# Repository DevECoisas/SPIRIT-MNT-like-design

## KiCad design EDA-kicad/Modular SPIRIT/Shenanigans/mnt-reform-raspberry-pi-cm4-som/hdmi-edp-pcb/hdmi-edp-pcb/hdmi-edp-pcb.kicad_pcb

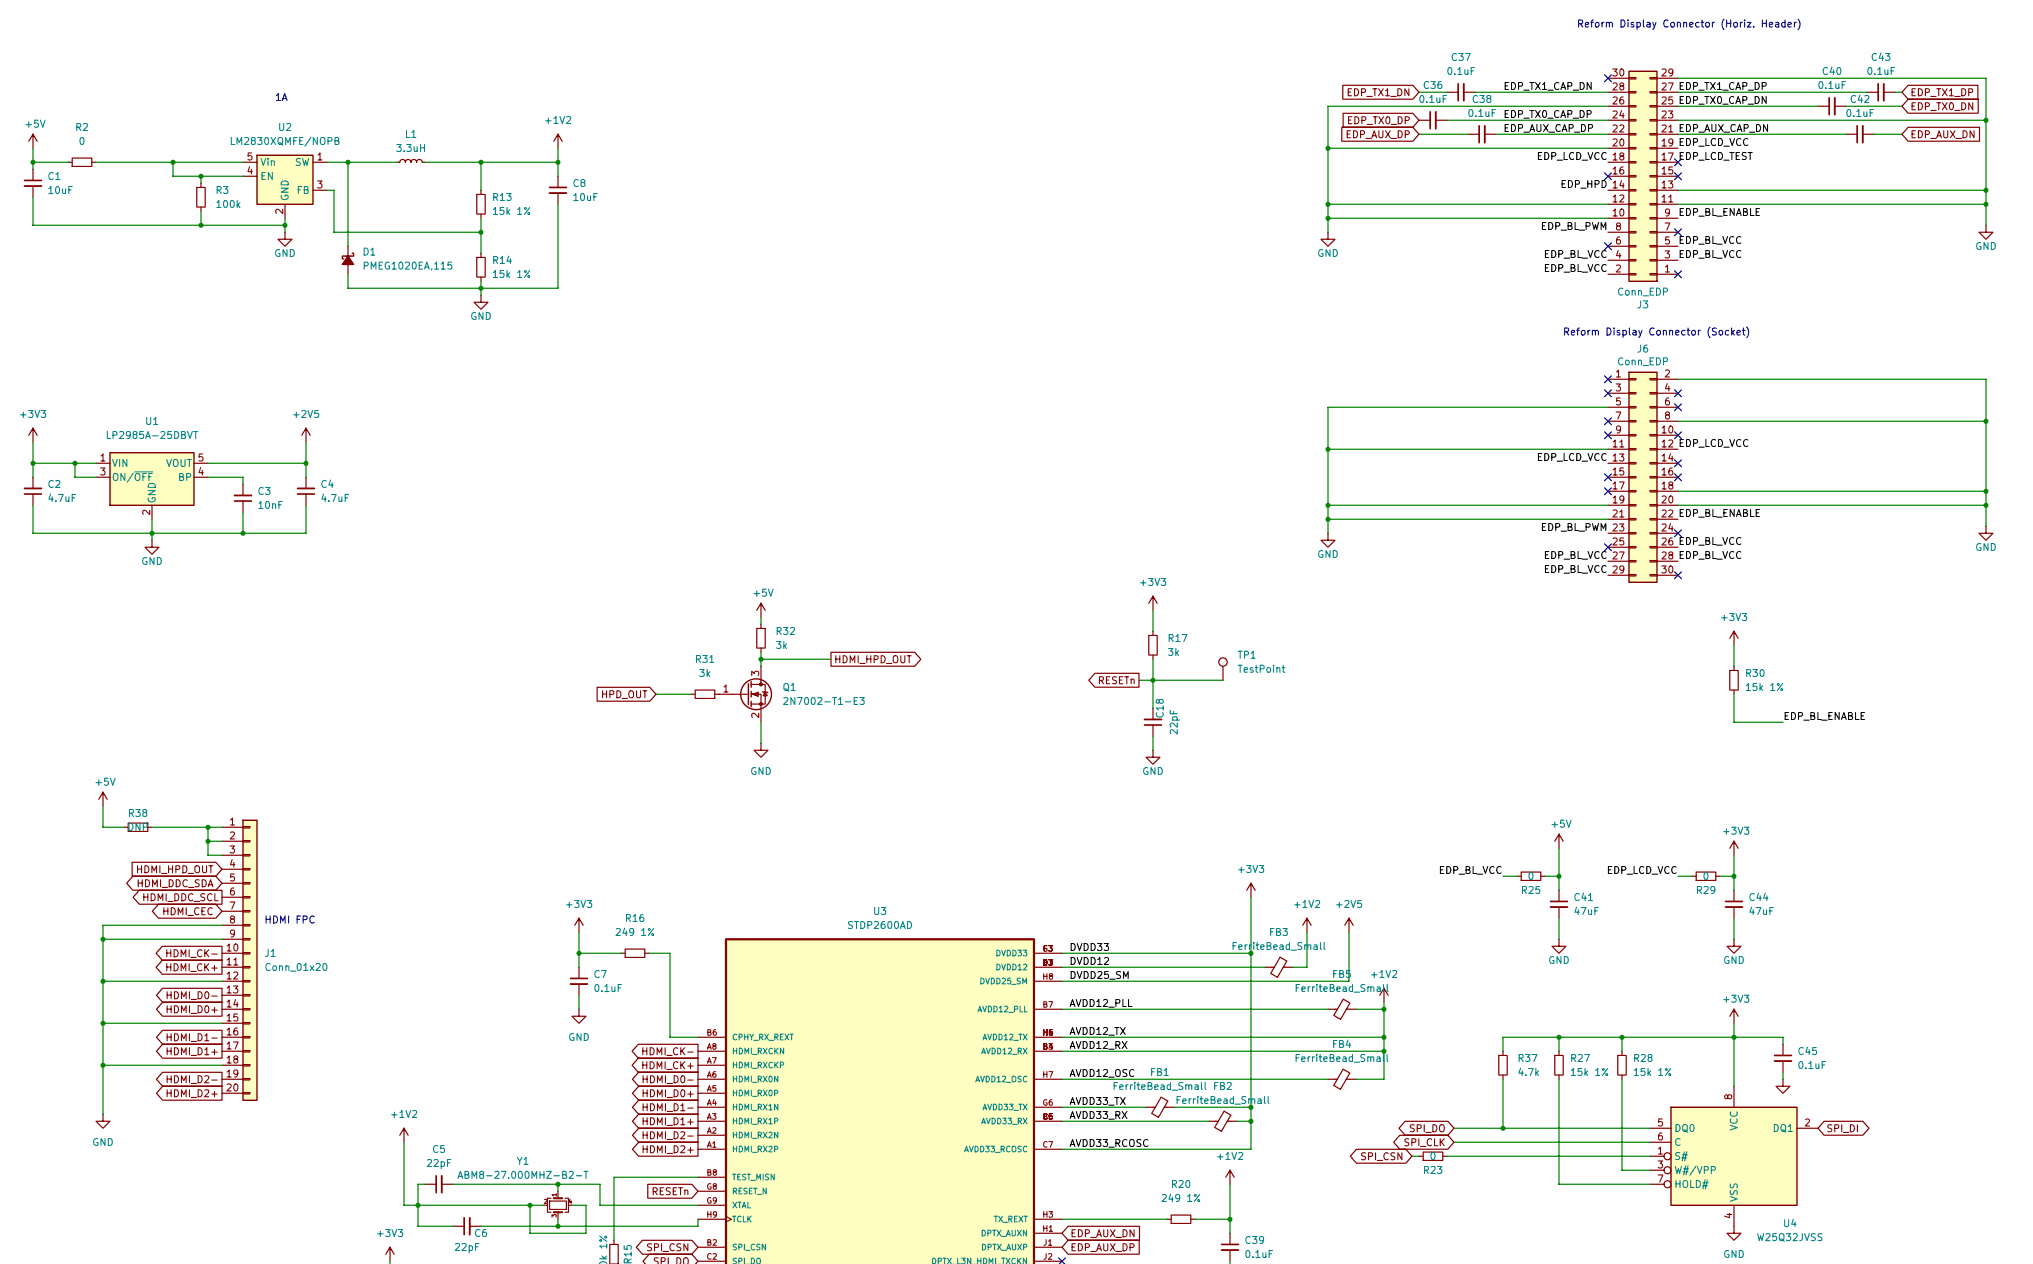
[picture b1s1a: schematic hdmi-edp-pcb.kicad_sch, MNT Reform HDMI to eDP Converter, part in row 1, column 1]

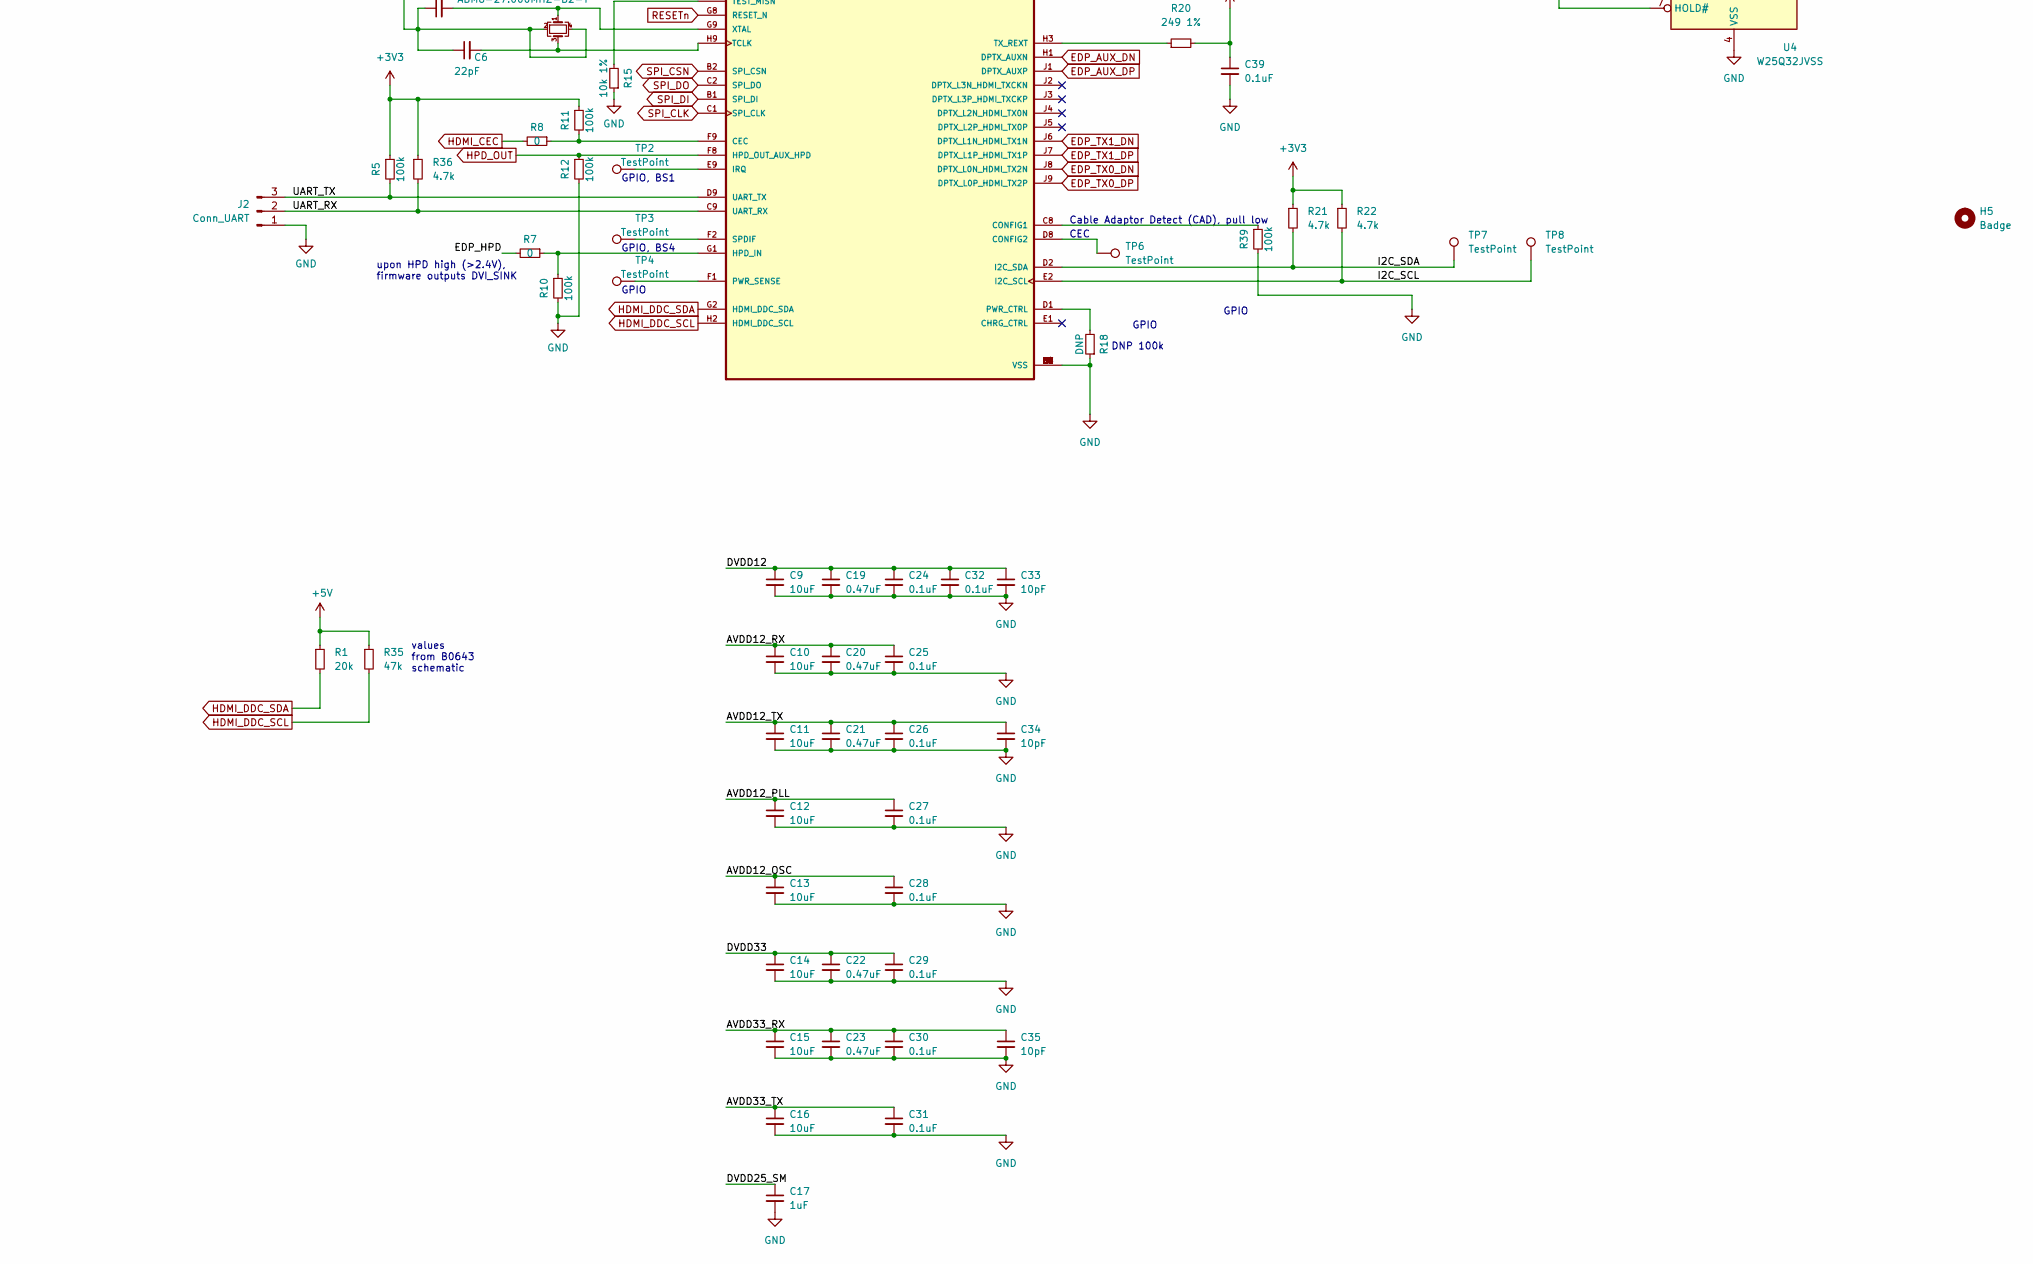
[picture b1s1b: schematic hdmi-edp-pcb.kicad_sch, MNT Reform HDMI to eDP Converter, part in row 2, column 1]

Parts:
C1, C8: 10uF; C_0603_1608Metric
C2, C4: 4.7uF; C_0402_1005Metric
C3: 10nF; C_0402_1005Metric
C5, C6, C18: 22pF; C_0402_1005Metric
C7, C24, C25, C26, C27, C28, C29, C30, C31, C32, C36, C37, C38, C39, C40, C42, C43, C45: 0.1uF; C_0402_1005Metric
C9, C10, C11, C12, C13, C14, C15, C16: 10uF; C_0402_1005Metric
C17: 1uF; C_0402_1005Metric
C19, C20, C21, C22, C23: 0.47uF; C_0402_1005Metric
C33, C34, C35: 10pF; C_0402_1005Metric
C41, C44: 47uF; C_0805_2012Metric
D1: PMEG1020EA,115; D_SOD-323
FB1, FB2, FB3, FB4, FB5: FerriteBead_Small; R_0603_1608Metric
H5: Badge; mnt-rhdp-badge-d1
J1: Conn_01x20; Hirose_FH12-20S-0.5SH_1x20-1MP_P0.50mm_Horizontal
J2: Conn_UART; PinHeader_1x03_P2.54mm_Vertical
J3: Conn_EDP; PinHeader_2x15_P2.00mm_Horizontal
J6: Conn_EDP; PinSocket_2x15_P2.00mm_Vertical
L1: 3.3uH; L_1210_3225Metric
Q1: 2N7002-T1-E3; SOT-23
R1: 20k; R_0603_1608Metric
R2, R7, R8, R23, R25, R29: 0; R_0603_1608Metric
R3, R5, R10, R11, R12, R39: 100k; R_0603_1608Metric
R13, R14, R27, R28, R30: 15k 1%; R_0603_1608Metric
R15: 10k 1%; R_0603_1608Metric
R16, R20: 249 1%; R_0603_1608Metric
R17, R31, R32: 3k; R_0603_1608Metric
R18, R38: DNP; R_0603_1608Metric
R21, R22, R36, R37: 4.7k; R_0603_1608Metric
R35: 47k; R_0603_1608Metric
TP1, TP2, TP3, TP4, TP6, TP7, TP8: TestPoint; TestPoint_Pad_D1.0mm
U1: LP2985A-25DBVT; SOT-23-5
U2: LM2830XQMFE/NOPB; SOT-23-5
U3: STDP2600AD; BGA81C80P9X9_800X800X140N
U4: W25Q32JVSS; SOIC-8W_5.3x5.3mm_P1.27mm
Y1: ABM8-27.000MHZ-B2-T; Crystal_SMD_3225-4Pin_3.2x2.5mm

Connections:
+1V2: C5.1, C6.1, C8.1, C10.1, C11.1, C20.1, C21.1, C25.1, C26.1, C34.1, C39.1, FB3.2, FB4.2, FB5.2, L1.2, R13.1, R20.2, U3.B3 (AVDD12_RX), U3.B4 (AVDD12_RX), U3.H4 (AVDD12_TX), U3.H5 (AVDD12_TX), U3.H6 (AVDD12_TX), Y1.2, Y1.4
+2V5: C4.2, C17.1, U1.5 (VOUT), U3.H8 (DVDD25_SM)
+3V3: C2.2, C7.1, C14.1, C22.1, C29.1, C44.1, C45.1, FB1.2, FB2.2, R5.1, R11.1, R16.1, R17.1, R21.1, R22.1, R27.1, R28.1, R29.2, R30.1, R36.1, R37.1, U1.1 (VIN), U1.3 (ON/~OFF), U3.C7 (AVDD33_RCOSC), U3.F3 (DVDD33), U3.G3 (DVDD33), U4.8 (VCC)
+5V: C1.1, C41.1, R1.1, R2.1, R25.2, R32.1, R35.1, R38.2
/AVDD12_OSC: C13.1, C28.1, FB4.1, U3.H7 (AVDD12_OSC)
/AVDD12_PLL: C12.1, C27.1, FB5.1, U3.B7 (AVDD12_PLL)
/AVDD33_RX: C15.1, C23.1, C30.1, C35.1, FB2.1, U3.B5 (AVDD33_RX), U3.C5 (AVDD33_RX), U3.C6 (AVDD33_RX)
/AVDD33_TX: C16.1, C31.1, FB1.1, U3.G6 (AVDD33_TX)
/DVDD12: C9.1, C19.1, C24.1, C32.1, C33.1, FB3.1, U3.D3 (DVDD12), U3.D7 (DVDD12), U3.E3 (DVDD12), U3.E7 (DVDD12)
/EDP_AUX_CAP_DN: C42.1, J3.21
/EDP_AUX_CAP_DP: C38.2, J3.22
/EDP_BL_ENABLE: J3.9, J6.22, R30.2
/EDP_BL_PWM: J3.8, J6.23
/EDP_BL_VCC: J3.2, J3.3, J3.4, J3.5, J6.26, J6.27, J6.28, J6.29, R25.1
/EDP_HPD: J3.14, R7.2
/EDP_LCD_TEST: J3.17
/EDP_LCD_VCC: J3.18, J3.19, J6.12, J6.13, R29.1
/EDP_TX0_CAP_DN: C40.1, J3.25
/EDP_TX0_CAP_DP: C36.2, J3.24
/EDP_TX1_CAP_DN: C37.2, J3.28
/EDP_TX1_CAP_DP: C43.1, J3.27
/I2C_SCL: R22.2, TP8.1, U3.E2 (I2C_SCL)
/I2C_SDA: R21.2, TP7.1, U3.D2 (I2C_SDA)
/UART_RX: J2.2, R36.2, U3.C9 (UART_RX)
/UART_TX: J2.3, R5.2, U3.D9 (UART_TX)
EDP_AUX_DN: C42.2, U3.H1 (DPTX_AUXN)
EDP_AUX_DP: C38.1, U3.J1 (DPTX_AUXP)
EDP_TX0_DN: C40.2, U3.J8 (DPTX_L0N_HDMI_TX2N)
EDP_TX0_DP: C36.1, U3.J9 (DPTX_L0P_HDMI_TX2P)
EDP_TX1_DN: C37.1, U3.J6 (DPTX_L1N_HDMI_TX1N)
EDP_TX1_DP: C43.2, U3.J7 (DPTX_L1P_HDMI_TX1P)
HDMI_CEC: J1.7, R8.2
HDMI_CK+: J1.11, U3.A7 (HDMI_RXCKP)
HDMI_CK-: J1.10, U3.A8 (HDMI_RXCKN)
HDMI_D0+: J1.14, U3.A5 (HDMI_RX0P)
HDMI_D0-: J1.13, U3.A6 (HDMI_RX0N)
HDMI_D1+: J1.17, U3.A3 (HDMI_RX1P)
HDMI_D1-: J1.16, U3.A4 (HDMI_RX1N)
HDMI_D2+: J1.20, U3.A1 (HDMI_RX2P)
HDMI_D2-: J1.19, U3.A2 (HDMI_RX2N)
HDMI_DDC_SCL: J1.6, R35.2, U3.H2 (HDMI_DDC_SCL)
HDMI_DDC_SDA: J1.5, R1.2, U3.G2 (HDMI_DDC_SDA)
HDMI_HPD_OUT: J1.4, Q1.3 (D), R32.2
HPD_OUT: R12.1, R31.2, U3.F8 (HPD_OUT_AUX_HPD)
unnamed: C3.2, U1.4 (BP)
unnamed: C5.2, U3.G9 (XTAL), Y1.1
unnamed: C6.2, U3.H9 (TCLK), Y1.3
unnamed: D1.1 (K), L1.1, U2.1 (SW)
unnamed: J1.1, J1.2, J1.3, R38.1
unnamed: Q1.1 (G), R31.1
unnamed: R2.2, R3.1, U2.4 (EN), U2.5 (Vin)
unnamed: R7.1, R10.1, U3.G1 (HPD_IN)
unnamed: R8.1, R11.2, U3.F9 (CEC)
unnamed: R13.2, R14.1, U2.3 (FB)
unnamed: R15.2, U3.B8 (TEST_MISN)
unnamed: R16.2, U3.B6 (CPHY_RX_REXT)
unnamed: R18.2, U3.D1 (PWR_CTRL)
unnamed: R20.1, U3.H3 (TX_REXT)
unnamed: R23.2, U4.1 (S#)
unnamed: R27.2, U4.7 (HOLD#)
unnamed: R28.2, U4.3 (W#/VPP)
unnamed: R39.1, U3.C8 (CONFIG1)
unnamed: TP2.1, U3.E9 (IRQ)
unnamed: TP3.1, U3.F2 (SPDIF)
unnamed: TP4.1, U3.F1 (PWR_SENSE)
unnamed: TP6.1, U3.D8 (CONFIG2)
RESETn: C18.2, R17.2, TP1.1, U3.G8 (RESET_N)
SPI_CLK: U3.C1 (SPI_CLK), U4.6 (C)
SPI_CSN: R23.1, U3.B2 (SPI_CSN)
SPI_DI: U3.B1 (SPI_DI), U4.2 (DQ1)
SPI_DO: R37.2, U3.C2 (SPI_DO), U4.5 (DQ0)

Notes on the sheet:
GPIO, BS4
GPIO
DNP 100k
Reform Display Connector (Horiz. Header)
GPIO, BS1
Cable Adaptor Detect (CAD), pull low
values from B0643 schematic
CEC
upon HPD high (>2.4V), firmware outputs DVI_SINK
HDMI FPC
Reform Display Connector (Socket)

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
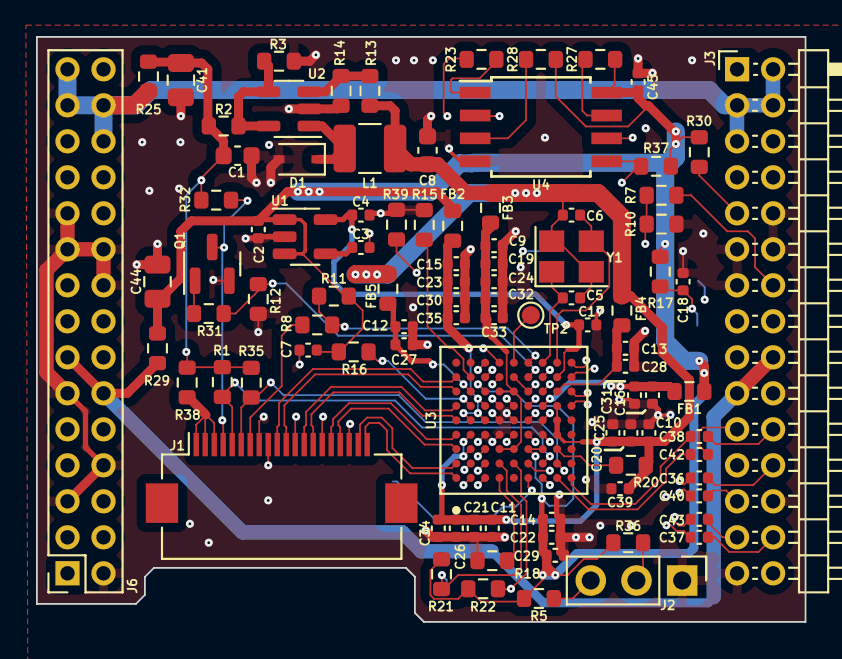
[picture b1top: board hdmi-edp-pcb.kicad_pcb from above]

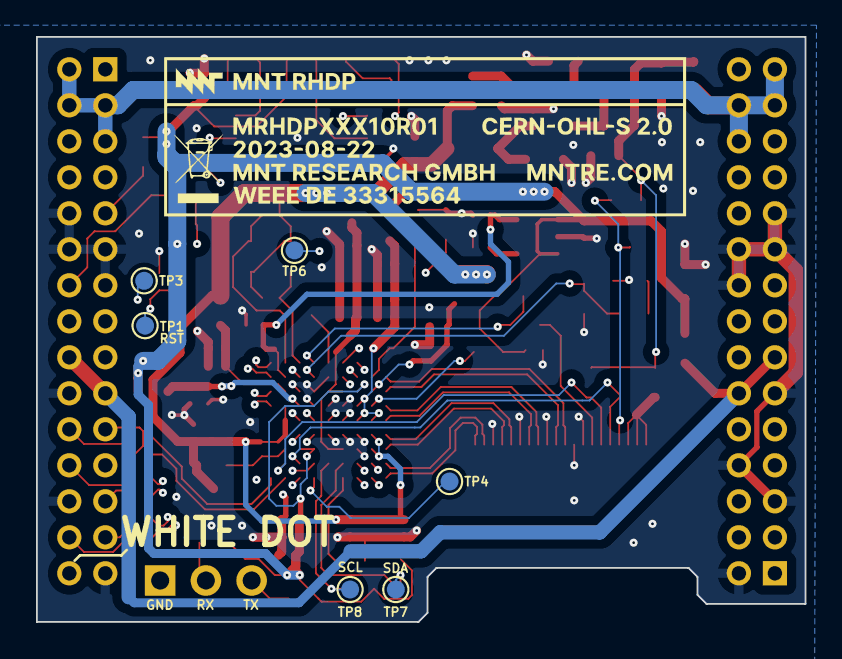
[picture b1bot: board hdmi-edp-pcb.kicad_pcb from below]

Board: 4 copper layers, 42.7 x 32.5 mm, 101 parts (7 on the bottom side), 71 nets.

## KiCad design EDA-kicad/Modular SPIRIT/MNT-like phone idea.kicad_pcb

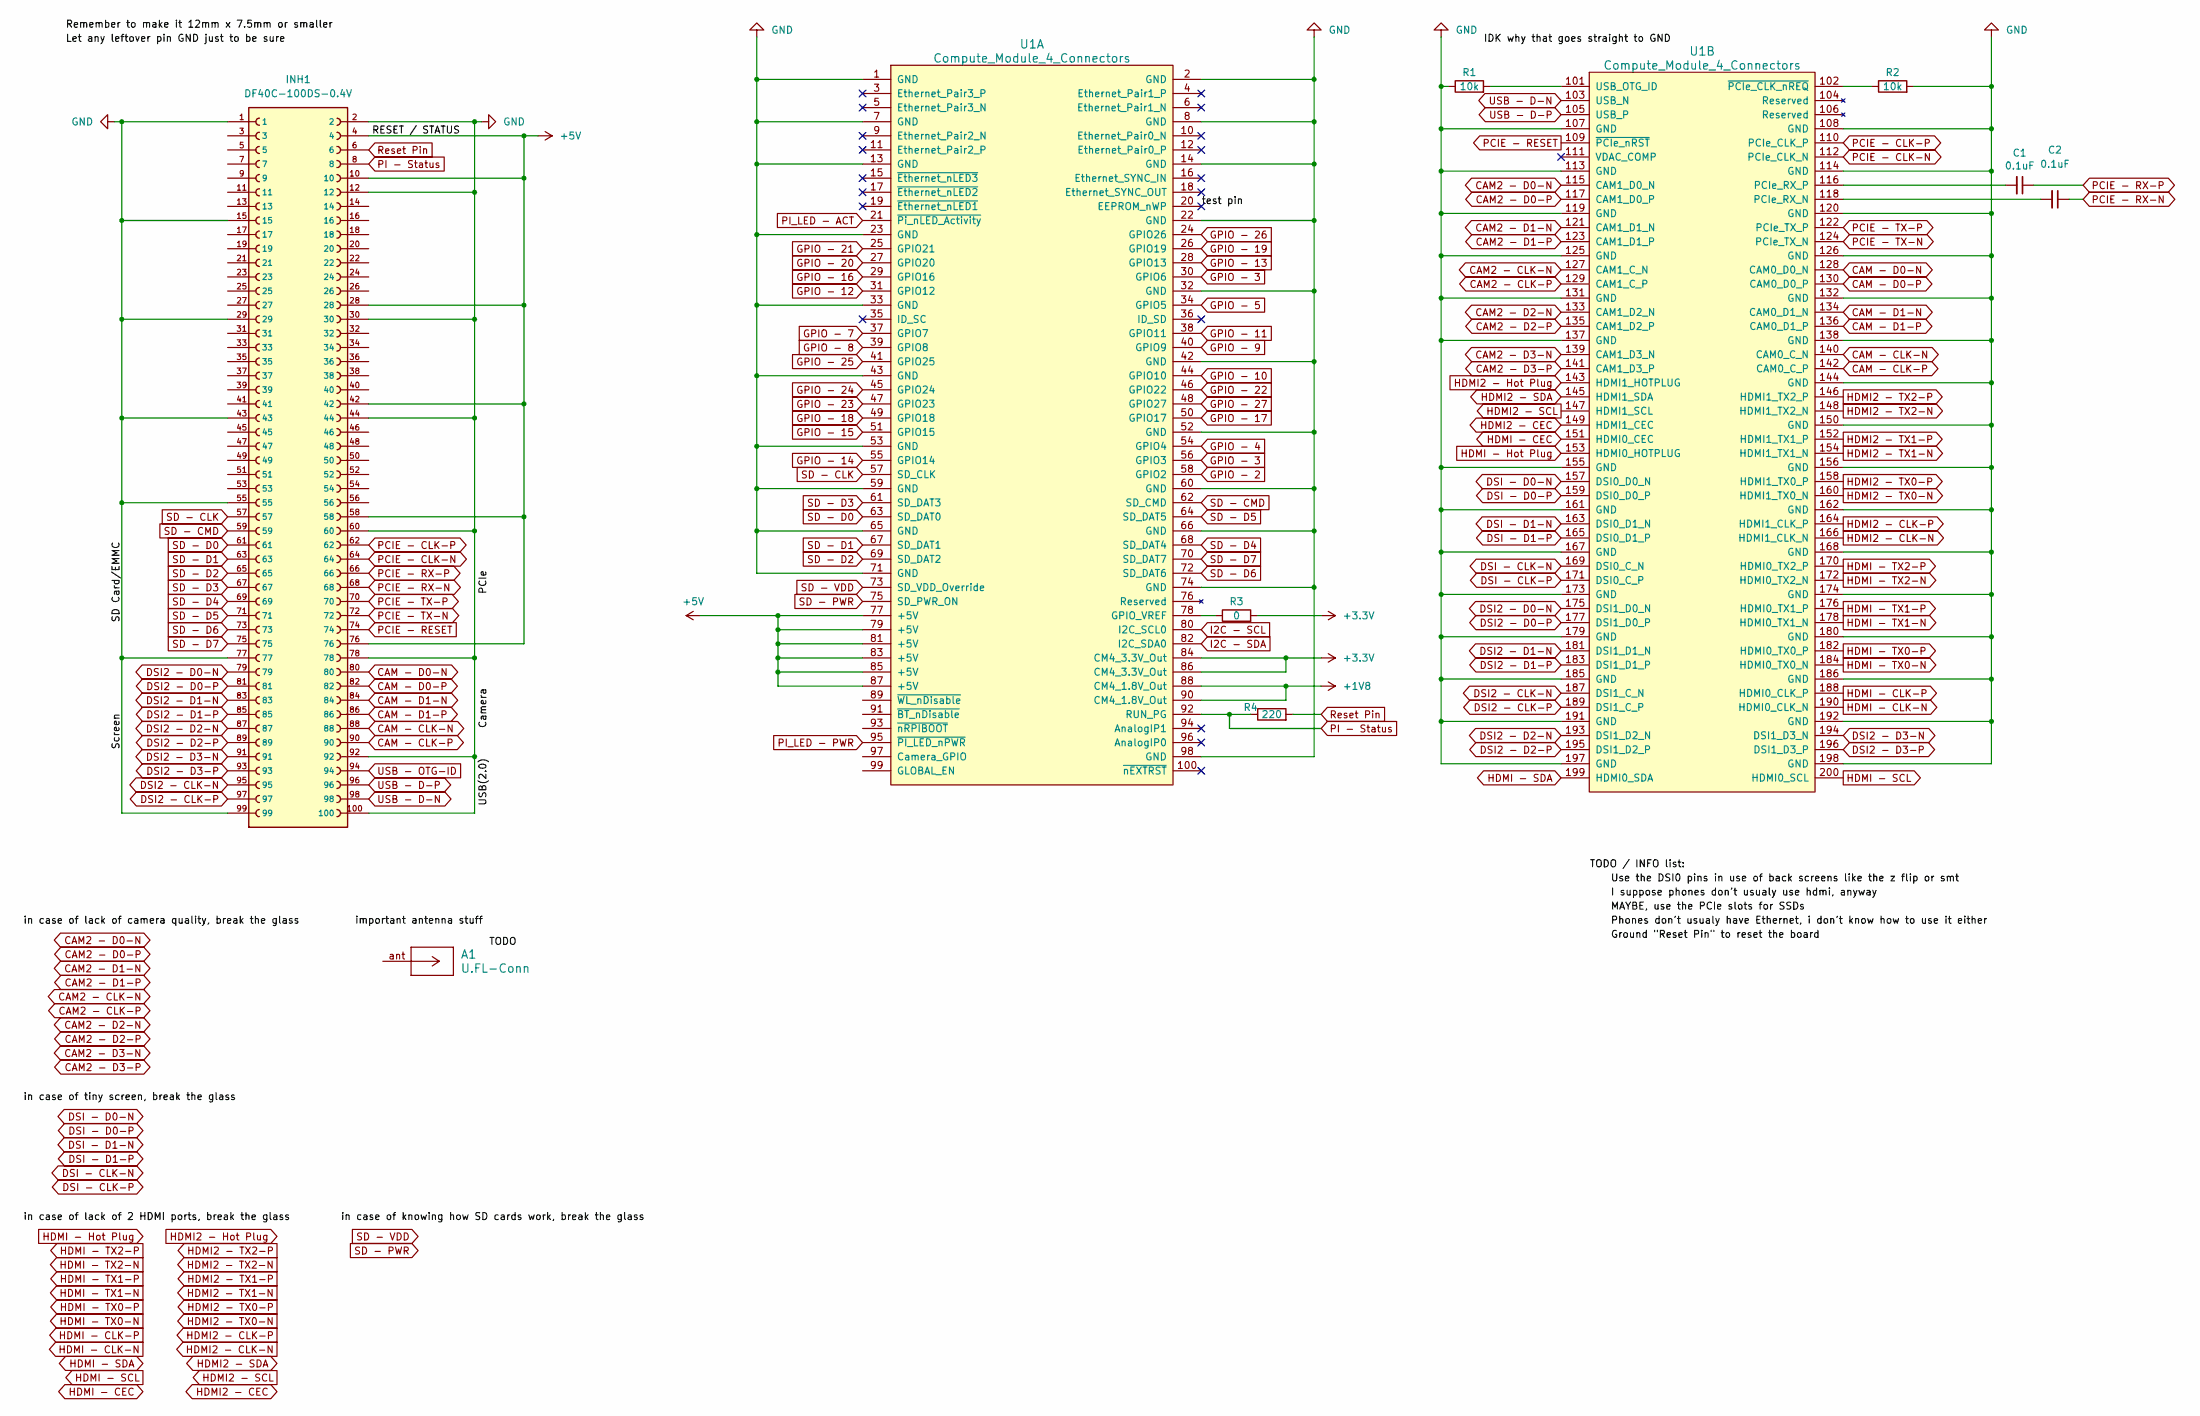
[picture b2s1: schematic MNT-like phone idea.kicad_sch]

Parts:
A1: U.FL-Conn; CONN1_UFL-R_HIR
C1, C2: 0.1uF; C_0805_2012Metric; MPN CC0402KRX7R7BB104; LCSC C60474
INH1: DF40C-100DS-0.4V; Hirose_DF40C-100DS-0.4V_2x50_P0.4mm; PARTREV Oct.1.2023
R1, R2: 10k; R_0805_2012Metric
R3: 0; R_0805_2012Metric
R4: 220; R_0805_2012Metric
U1: Compute_Module_4_Connectors; Raspberry-Pi-4-Compute-Module

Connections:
+1V8: U1.88 (CM4_1.8V_Out), U1.90 (CM4_1.8V_Out)
+3.3V: R3.2, U1.84 (CM4_3.3V_Out), U1.86 (CM4_3.3V_Out)
+5V: INH1.4, INH1.10, INH1.28, INH1.42, INH1.58, INH1.76, U1.77 (+5V), U1.79 (+5V), U1.81 (+5V), U1.83 (+5V), U1.85 (+5V), U1.87 (+5V)
/test pin: U1.20 (EEPROM_nWP)
CAM2 - CLK-N: U1.127 (CAM1_C_N)
CAM2 - CLK-P: U1.129 (CAM1_C_P)
CAM2 - D0-N: U1.115 (CAM1_D0_N)
CAM2 - D0-P: U1.117 (CAM1_D0_P)
CAM2 - D1-N: U1.121 (CAM1_D1_N)
CAM2 - D1-P: U1.123 (CAM1_D1_P)
CAM2 - D2-N: U1.133 (CAM1_D2_N)
CAM2 - D2-P: U1.135 (CAM1_D2_P)
CAM2 - D3-N: U1.139 (CAM1_D3_N)
CAM2 - D3-P: U1.141 (CAM1_D3_P)
CAM - CLK-N: INH1.88, U1.140 (CAM0_C_N)
CAM - CLK-P: INH1.90, U1.142 (CAM0_C_P)
CAM - D0-N: INH1.80, U1.128 (CAM0_D0_N)
CAM - D0-P: INH1.82, U1.130 (CAM0_D0_P)
CAM - D1-N: INH1.84, U1.134 (CAM0_D1_N)
CAM - D1-P: INH1.86, U1.136 (CAM0_D1_P)
DSI2 - CLK-N: INH1.95, U1.187 (DSI1_C_N)
DSI2 - CLK-P: INH1.97, U1.189 (DSI1_C_P)
DSI2 - D0-N: INH1.79, U1.175 (DSI1_D0_N)
DSI2 - D0-P: INH1.81, U1.177 (DSI1_D0_P)
DSI2 - D1-N: INH1.83, U1.181 (DSI1_D1_N)
DSI2 - D1-P: INH1.85, U1.183 (DSI1_D1_P)
DSI2 - D2-N: INH1.87, U1.193 (DSI1_D2_N)
DSI2 - D2-P: INH1.89, U1.195 (DSI1_D2_P)
DSI2 - D3-N: INH1.91, U1.194 (DSI1_D3_N)
DSI2 - D3-P: INH1.93, U1.196 (DSI1_D3_P)
DSI - CLK-N: U1.169 (DSI0_C_N)
DSI - CLK-P: U1.171 (DSI0_C_P)
DSI - D0-N: U1.157 (DSI0_D0_N)
DSI - D0-P: U1.159 (DSI0_D0_P)
DSI - D1-N: U1.163 (DSI0_D1_N)
DSI - D1-P: U1.165 (DSI0_D1_P)
GND: INH1.1, INH1.2, INH1.12, INH1.15, INH1.29, INH1.30, INH1.43, INH1.44, INH1.55, INH1.60, INH1.77, INH1.78, INH1.92, INH1.99, INH1.100, R1.1, R2.2, U1.1 (GND), U1.2 (GND), U1.7 (GND), U1.8 (GND), U1.13 (GND), U1.14 (GND), U1.22 (GND), U1.23 (GND), U1.32 (GND), U1.33 (GND), U1.42 (GND), U1.43 (GND), U1.52 (GND), U1.53 (GND), U1.59 (GND), U1.60 (GND), U1.65 (GND), U1.66 (GND), U1.71 (GND), U1.74 (GND), U1.98 (GND), U1.107 (GND), U1.108 (GND), U1.113 (GND), U1.114 (GND), U1.119 (GND), U1.120 (GND), U1.125 (GND), U1.126 (GND), U1.131 (GND), U1.132 (GND), U1.137 (GND), U1.138 (GND), U1.144 (GND), U1.150 (GND), U1.155 (GND), U1.156 (GND), U1.161 (GND), U1.162 (GND), U1.167 (GND), U1.168 (GND), U1.173 (GND), U1.174 (GND), U1.179 (GND), U1.180 (GND), U1.185 (GND), U1.186 (GND), U1.191 (GND), U1.192 (GND), U1.197 (GND), U1.198 (GND)
GPIO - 2: U1.58 (GPIO2)
GPIO - 3: U1.30 (GPIO6), U1.56 (GPIO3)
GPIO - 4: U1.54 (GPIO4)
GPIO - 5: U1.34 (GPIO5)
GPIO - 7: U1.37 (GPIO7)
GPIO - 8: U1.39 (GPIO8)
GPIO - 9: U1.40 (GPIO9)
GPIO - 10: U1.44 (GPIO10)
GPIO - 11: U1.38 (GPIO11)
GPIO - 12: U1.31 (GPIO12)
GPIO - 13: U1.28 (GPIO13)
GPIO - 14: U1.55 (GPIO14)
GPIO - 15: U1.51 (GPIO15)
GPIO - 16: U1.29 (GPIO16)
GPIO - 17: U1.50 (GPIO17)
GPIO - 18: U1.49 (GPIO18)
GPIO - 19: U1.26 (GPIO19)
GPIO - 20: U1.27 (GPIO20)
GPIO - 21: U1.25 (GPIO21)
GPIO - 22: U1.46 (GPIO22)
GPIO - 23: U1.47 (GPIO23)
GPIO - 24: U1.45 (GPIO24)
GPIO - 25: U1.41 (GPIO25)
GPIO - 26: U1.24 (GPIO26)
GPIO - 27: U1.48 (GPIO27)
HDMI2 - CEC: U1.149 (HDMI1_CEC)
HDMI2 - CLK-N: U1.166 (HDMI1_CLK_N)
HDMI2 - CLK-P: U1.164 (HDMI1_CLK_P)
HDMI2 - Hot Plug: U1.143 (HDMI1_HOTPLUG)
HDMI2 - SCL: U1.147 (HDMI1_SCL)
HDMI2 - SDA: U1.145 (HDMI1_SDA)
HDMI2 - TX0-N: U1.160 (HDMI1_TX0_N)
HDMI2 - TX0-P: U1.158 (HDMI1_TX0_P)
HDMI2 - TX1-N: U1.154 (HDMI1_TX1_N)
HDMI2 - TX1-P: U1.152 (HDMI1_TX1_P)
HDMI2 - TX2-N: U1.148 (HDMI1_TX2_N)
HDMI2 - TX2-P: U1.146 (HDMI1_TX2_P)
HDMI - CEC: U1.151 (HDMI0_CEC)
HDMI - CLK-N: U1.190 (HDMI0_CLK_N)
HDMI - CLK-P: U1.188 (HDMI0_CLK_P)
HDMI - Hot Plug: U1.153 (HDMI0_HOTPLUG)
HDMI - SCL: U1.200 (HDMI0_SCL)
HDMI - SDA: U1.199 (HDMI0_SDA)
HDMI - TX0-N: U1.184 (HDMI0_TX0_N)
HDMI - TX0-P: U1.182 (HDMI0_TX0_P)
HDMI - TX1-N: U1.178 (HDMI0_TX1_N)
HDMI - TX1-P: U1.176 (HDMI0_TX1_P)
HDMI - TX2-N: U1.172 (HDMI0_TX2_N)
HDMI - TX2-P: U1.170 (HDMI0_TX2_P)
I2C - SCL: U1.80 (I2C_SCL0)
I2C - SDA: U1.82 (I2C_SDA0)
unnamed: R3.1, U1.78 (GPIO_VREF)
unnamed: C2.2, U1.118 (PCIe_RX_N)
unnamed: C1.2, U1.116 (PCIe_RX_P)
unnamed: R1.2, U1.101 (USB_OTG_ID)
unnamed: R2.1, U1.102 (~PCIe_CLK_nREQ)
PCIE - CLK-N: INH1.64, U1.112 (PCIe_CLK_N)
PCIE - CLK-P: INH1.62, U1.110 (PCIe_CLK_P)
PCIE - RESET: INH1.74, U1.109 (~PCIe_nRST)
PCIE - RX-N: C2.1, INH1.68
PCIE - RX-P: C1.1, INH1.66
PCIE - TX-N: INH1.72, U1.124 (PCIe_TX_N)
PCIE - TX-P: INH1.70, U1.122 (PCIe_TX_P)
PI - Status: INH1.8, R4.1, U1.92 (RUN_PG)
PI_LED - ACT: U1.21 (~Pi_nLED_Activity)
PI_LED - PWR: U1.95 (~PI_LED_nPWR)
Reset Pin: INH1.6, R4.2
SD - CLK: INH1.57, U1.57 (SD_CLK)
SD - CMD: INH1.59, U1.62 (SD_CMD)
SD - D0: INH1.61, U1.63 (SD_DAT0)
SD - D1: INH1.63, U1.67 (SD_DAT1)
SD - D2: INH1.65, U1.69 (SD_DAT2)
SD - D3: INH1.67, U1.61 (SD_DAT3)
SD - D4: INH1.69, U1.68 (SD_DAT4)
SD - D5: INH1.71, U1.64 (SD_DAT5)
SD - D6: INH1.73, U1.72 (SD_DAT6)
SD - D7: INH1.75, U1.70 (SD_DAT7)
SD - PWR: U1.75 (SD_PWR_ON)
SD - VDD: U1.73 (SD_VDD_Override)
USB - D-N: INH1.98, U1.103 (USB_N)
USB - D-P: INH1.96, U1.105 (USB_P)
USB - OTG-ID: INH1.94

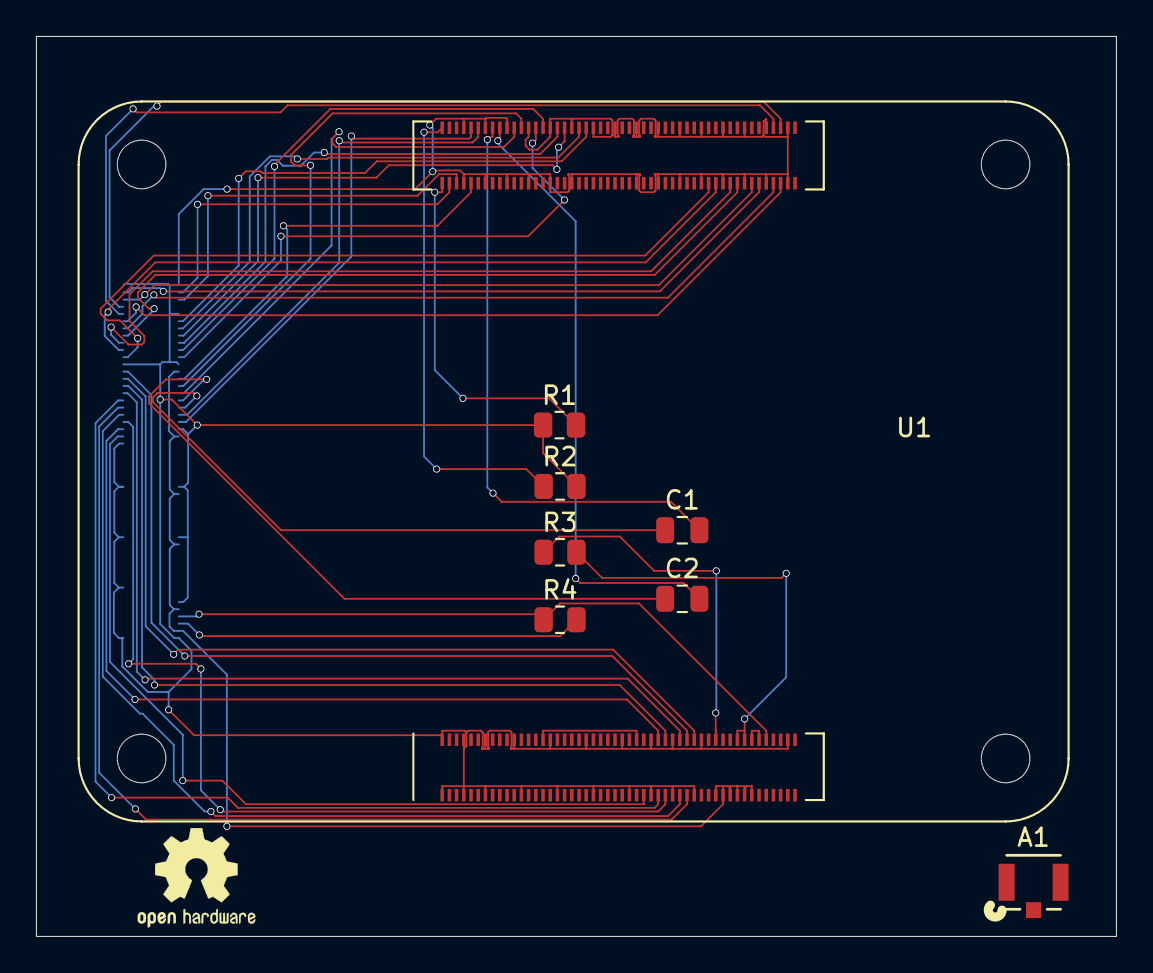
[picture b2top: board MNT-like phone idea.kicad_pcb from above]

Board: 2 copper layers, 60.0 x 50.0 mm, 9 parts (1 on the bottom side), 47 nets.

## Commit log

2025-10-18 The Schematics of the idea
2025-10-18 Neating up some things
2025-10-19 neating up some files
2025-10-29 removing some files

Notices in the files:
EDA-kicad/Modular SPIRIT/Shenanigans/mnt-reform-raspberry-pi-cm4-som/hdmi-edp-pcb/hdmi-edp-pcb/hdmi-edp-pcb.kicad_sch:
License: CERN-OHL-S 2.0
